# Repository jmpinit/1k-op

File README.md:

# 1K-OP

A little programmable computer-toy for your pocket. I hope that it contains a little bit of the deep joy and obsession that I have for computers. 

The hardware provides a little display and speaker for output, and 8 buttons for input. 

The software provides a (very) minimal Forth-like programming environment. 

**Inspirations:**

* Teenage Engineering OP-1 
* John Earnest's Mako virtual game console 
* TI-83+-induced carpal tunnel, and buttons worn illegible

[Project on Hackaday.io](https://hackaday.io/project/19215).

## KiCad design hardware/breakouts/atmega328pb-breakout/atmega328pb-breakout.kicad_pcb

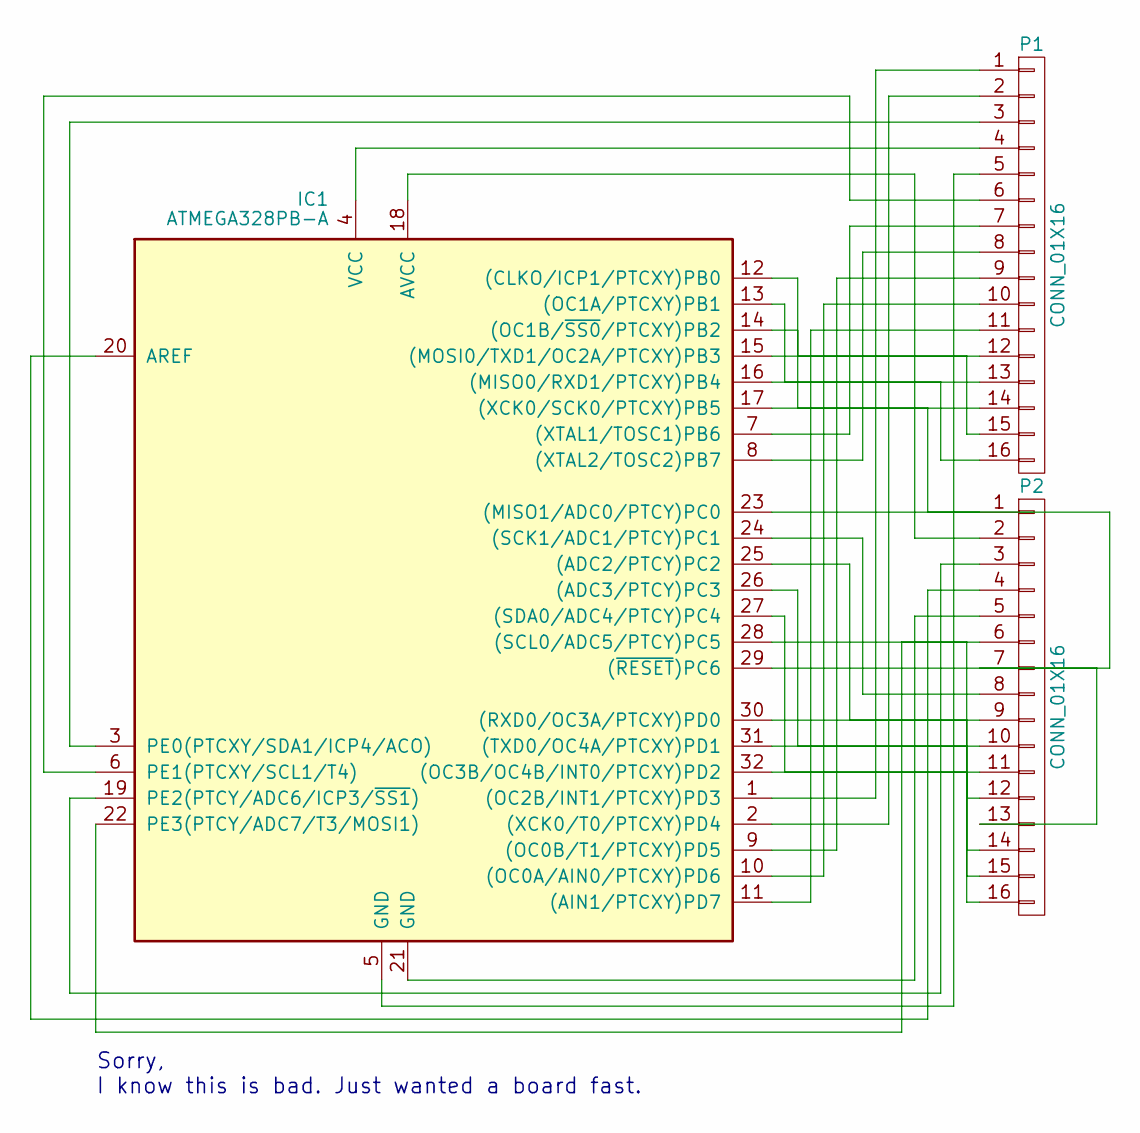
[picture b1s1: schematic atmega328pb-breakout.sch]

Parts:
IC1: ATMEGA328PB-A; TQFP-32_7x7mm_Pitch0.8mm
P1, P2: CONN_01X16; Pin_Header_Straight_1x16

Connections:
unnamed: IC1.1 ((OC2B/INT1/PTCXY)PD3), P1.1
unnamed: IC1.2 ((XCK0/T0/PTCXY)PD4), P1.2
unnamed: IC1.3 (PE0(PTCXY/SDA1/ICP4/ACO)), P1.3
unnamed: IC1.4 (VCC), P1.4
unnamed: IC1.5 (GND), P1.5
unnamed: IC1.6 (PE1(PTCXY/SCL1/T4)), P1.6
unnamed: IC1.7 ((XTAL1/TOSC1)PB6), P1.7
unnamed: IC1.8 ((XTAL2/TOSC2)PB7), P1.8
unnamed: IC1.9 ((OC0B/T1/PTCXY)PD5), P1.9
unnamed: IC1.10 ((OC0A/AIN0/PTCXY)PD6), P1.10
unnamed: IC1.11 ((AIN1/PTCXY)PD7), P1.11
unnamed: IC1.12 ((CLKO/ICP1/PTCXY)PB0), P1.12
unnamed: IC1.13 ((OC1A/PTCXY)PB1), P1.13
unnamed: IC1.14 ((OC1B/~SS0~/PTCXY)PB2), P1.14
unnamed: IC1.15 ((MOSI0/TXD1/OC2A/PTCXY)PB3), P1.15
unnamed: IC1.16 ((MISO0/RXD1/PTCXY)PB4), P1.16
unnamed: IC1.17 ((XCK0/SCK0/PTCXY)PB5), P2.1
unnamed: IC1.18 (AVCC), P2.2
unnamed: IC1.19 (PE2(PTCY/ADC6/ICP3/~SS1~)), P2.3
unnamed: IC1.20 (AREF), P2.4
unnamed: IC1.21 (GND), P2.5
unnamed: IC1.22 (PE3(PTCY/ADC7/T3/MOSI1)), P2.6
unnamed: IC1.23 ((MISO1/ADC0/PTCY)PC0), P2.7
unnamed: IC1.24 ((SCK1/ADC1/PTCY)PC1), P2.8
unnamed: IC1.25 ((ADC2/PTCY)PC2), P2.9
unnamed: IC1.26 ((ADC3/PTCY)PC3), P2.10
unnamed: IC1.27 ((SDA0/ADC4/PTCY)PC4), P2.11
unnamed: IC1.28 ((SCL0/ADC5/PTCY)PC5), P2.12
unnamed: IC1.29 ((~RESET~)PC6), P2.13
unnamed: IC1.30 ((RXD0/OC3A/PTCXY)PD0), P2.14
unnamed: IC1.31 ((TXD0/OC4A/PTCXY)PD1), P2.15
unnamed: IC1.32 ((OC3B/OC4B/INT0/PTCXY)PD2), P2.16

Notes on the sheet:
Sorry, I know this is bad. Just wanted a board fast.

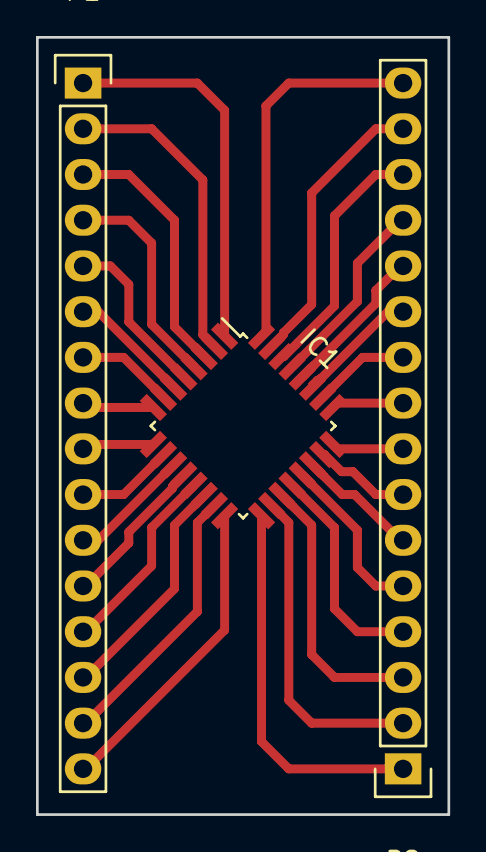
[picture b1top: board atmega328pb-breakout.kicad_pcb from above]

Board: 2 copper layers, 22.9 x 43.2 mm, 3 parts (0 on the bottom side), 32 nets.

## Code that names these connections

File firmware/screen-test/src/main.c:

#include <stdlib.h>
#include <stdint.h>
#include <avr/io.h>
#include <util/delay.h>
#include <avr/pgmspace.h>

#include "boxer.h"

#define WIDTH 96
#define HEIGHT 96

#define SHARPMEM_BIT_WRITECMD   (1)
#define SHARPMEM_BIT_VCOM       (1 << 1)
#define SHARPMEM_BIT_CLEAR      (1 << 2)

#define PIN_LED PD2

#define PIN_CS PC0
#define PIN_CLK PC1
#define PIN_DOUT PC2

#define cbi(sfr, bit) (_SFR_BYTE(sfr) &= ~_BV(bit))
#define sbi(sfr, bit) (_SFR_BYTE(sfr) |= _BV(bit))

#define forever for(;;)

uint8_t currentVcom = 0;

void clkLow() {
  cbi(PORTC, PIN_CLK);
}

void clkHigh() {
  sbi(PORTC, PIN_CLK);
}

void dataLow() {
  cbi(PORTC, PIN_DOUT);
}

void dataHigh() {
  sbi(PORTC, PIN_DOUT);
}

void select() {
  sbi(PORTC, PIN_CS);
}

void deselect() {
  cbi(PORTC, PIN_CS);
}

void send_byte(uint8_t data) {
  for (int i = 0; i < 8; i++) {
    clkLow();

    if (data & 1) {
      dataHigh();
    } else {
      dataLow();
    }

    clkHigh();
    data >>= 1;
  }

  clkLow();
}

void clear() {
  select();
  send_byte(currentVcom | SHARPMEM_BIT_CLEAR);
  currentVcom = currentVcom ? 0 : SHARPMEM_BIT_VCOM;
  send_byte(0);
  deselect();
}

/*
void refresh() {
  uint16_t i, totalbytes, currentline, oldline;  
  totalbytes = (WIDTH * HEIGHT) / 8;

  // Send the write command
  select();
  send_byte(SHARPMEM_BIT_WRITECMD | currentVcom);
  currentVcom = currentVcom ? 0 : SHARPMEM_BIT_VCOM;

  // Send the address for line 1
  oldline = currentline = 1;
  send_byte(currentline);

  // Send image buffer
  for (i=0; i<totalbytes; i++) {
    send_byte(0xAA);
    currentline = ((i+1)/(WIDTH/8)) + 1;
    if(currentline != oldline) {
      // Send end of line and address bytes
      send_byte(0x00);
      if (currentline <= HEIGHT) {
        send_byte(currentline);
      }
      oldline = currentline;
    }
  }

  // Send another trailing 8 bits for the last line
  send_byte(0x00);
  deselect();
}
*/

void drawBoxer() {
  select();
  send_byte(currentVcom | SHARPMEM_BIT_WRITECMD);
  currentVcom = currentVcom ? 0 : SHARPMEM_BIT_VCOM;

  send_byte(1);

  int i = 0;
  for (int row = 0; row < HEIGHT; row++) {
    for (int col = 0; col < WIDTH / 8; col++) {
      send_byte(pgm_read_byte_near(boxer + i++));
    }

    send_byte(0);
    send_byte(row);
  }

  send_byte(0);

  deselect();
}

int main() {
  DDRD |= 1 << PD2;

  sbi(PORTC, PIN_CS);
  cbi(PORTC, PIN_CLK);
  sbi(PORTC, PIN_DOUT);

  sbi(DDRC, PIN_CS);
  sbi(DDRC, PIN_CLK);
  sbi(DDRC, PIN_DOUT);

  clear();

  forever {
    PORTD |= 1 << PD2;
    drawBoxer();
    PORTD &= ~(1 << PD2);
    _delay_ms(500);
  }

  return 0;
}

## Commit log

2017-01-03 Breakouts for MCU and EEPROM
2017-01-03 Image output on Sharp Memory LCD
2017-01-03 Explanation
2017-01-03 Adapt for context
2021-09-19 Add render
